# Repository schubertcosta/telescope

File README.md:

# telescope
My personal telescope project

#1 Step 1
    - check/change variables inside the constants.py

#2 Make sure your bluetooth is connected with your machine

#3 Run commands
    - Simulation mode: py -3.8 start.py
    - Analysis mode: py start.py -a

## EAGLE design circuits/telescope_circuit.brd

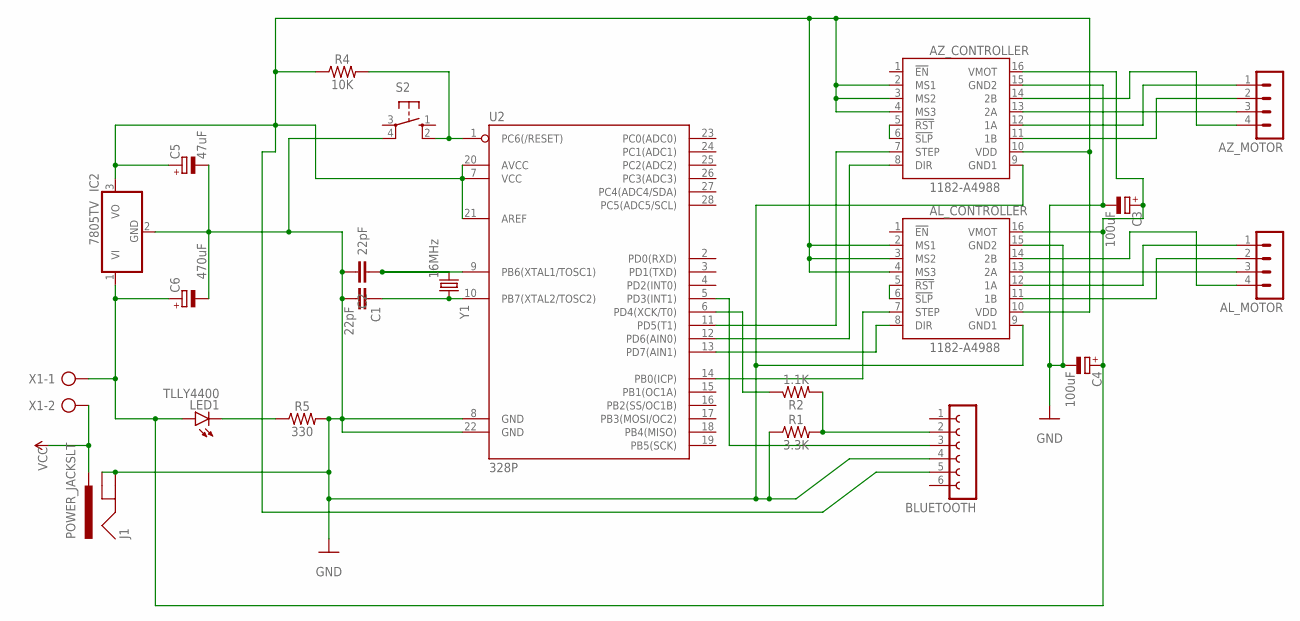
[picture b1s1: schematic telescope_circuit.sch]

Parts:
AL_CONTROLLER: 1182-A4988; A4988
AL_MOTOR: MA04-1
AZ_CONTROLLER: 1182-A4988; A4988
AZ_MOTOR: MA04-1
BLUETOOTH: FE06W
C1, C2: 22pF; CAP-PTH-2.54
C3, C4: 100uF; E2,5-6
C5: 47uF; E2,5-6
C6: 470uF; E2,5-6
IC2: 7805TV; TO220V
J1: POWER_JACKSLT; POWER_JACK_SLOT
LED1: TLLY4400; LED3MM
R1: 3.3K; AXIAL-0.3
R2: 1.1K; AXIAL-0.3
R4: 10K; AXIAL-0.3
R5: 330; AXIAL-0.3
S2: 10-XX; B3F-10XX
U2: 328P; DIP28
X1: AK500/2
Y1: 16MHz; HC49US

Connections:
GND: AL_CONTROLLER.9 (GND1), AL_CONTROLLER.15 (GND2), AZ_CONTROLLER.9 (GND1), AZ_CONTROLLER.15 (GND2), BLUETOOTH.4, C1.2, C2.2, C3.-, C4.-, C5.-, C6.-, IC2.2 (GND), J1.GND@1 (GNDBREAK), J1.GND@2 (GND), R1.P$1 (1), R5.P$2 (2), S2.4 (P1), U2.8 (GND), U2.22 (GND)
unnamed: C1.1, U2.10 (PB7(XTAL2/TOSC2)), Y1.2
unnamed: C2.1, U2.9 (PB6(XTAL1/TOSC1)), Y1.1
unnamed: AZ_CONTROLLER.7 (STEP), U2.11 (PD5(T1))
unnamed: BLUETOOTH.2, R1.P$2 (2), R2.P$2 (2)
unnamed: R4.P$2 (2), S2.2 (S1), U2.1 (PC6(/RESET))
unnamed: R2.P$1 (1), U2.6 (PD4(XCK/T0))
unnamed: AL_CONTROLLER.2 (MS1), AL_CONTROLLER.3 (MS2), AL_CONTROLLER.4 (MS3), AL_CONTROLLER.10 (VDD), AZ_CONTROLLER.2 (MS1), AZ_CONTROLLER.3 (MS2), AZ_CONTROLLER.4 (MS3), AZ_CONTROLLER.10 (VDD), BLUETOOTH.5, C5.+, IC2.3 (VO), R4.P$1 (1), U2.7 (VCC), U2.20 (AVCC), U2.21 (AREF)
unnamed: BLUETOOTH.3, U2.5 (PD3(INT1))
unnamed: AL_CONTROLLER.16 (VMOT), AZ_CONTROLLER.16 (VMOT), C3.+, C4.+, C6.+, IC2.1 (VI), LED1.A, X1.1
unnamed: AZ_CONTROLLER.8 (DIR), U2.12 (PD6(AIN0))
unnamed: AZ_CONTROLLER.5 (!RST), AZ_CONTROLLER.6 (!SLP)
unnamed: AZ_CONTROLLER.12 (1A), AZ_MOTOR.1
unnamed: AZ_CONTROLLER.11 (1B), AZ_MOTOR.2
unnamed: LED1.K (C), R5.P$1 (1)
unnamed: AZ_CONTROLLER.13 (2A), AZ_MOTOR.3
unnamed: AZ_CONTROLLER.14 (2B), AZ_MOTOR.4
unnamed: AL_CONTROLLER.8 (DIR), U2.13 (PD7(AIN1))
unnamed: AL_CONTROLLER.5 (!RST), AL_CONTROLLER.6 (!SLP)
unnamed: AL_CONTROLLER.7 (STEP), U2.14 (PB0(ICP))
unnamed: AL_CONTROLLER.12 (1A), AL_MOTOR.1
unnamed: AL_CONTROLLER.11 (1B), AL_MOTOR.2
unnamed: AL_CONTROLLER.13 (2A), AL_MOTOR.3
unnamed: AL_CONTROLLER.14 (2B), AL_MOTOR.4
VCC: J1.PWR, X1.2

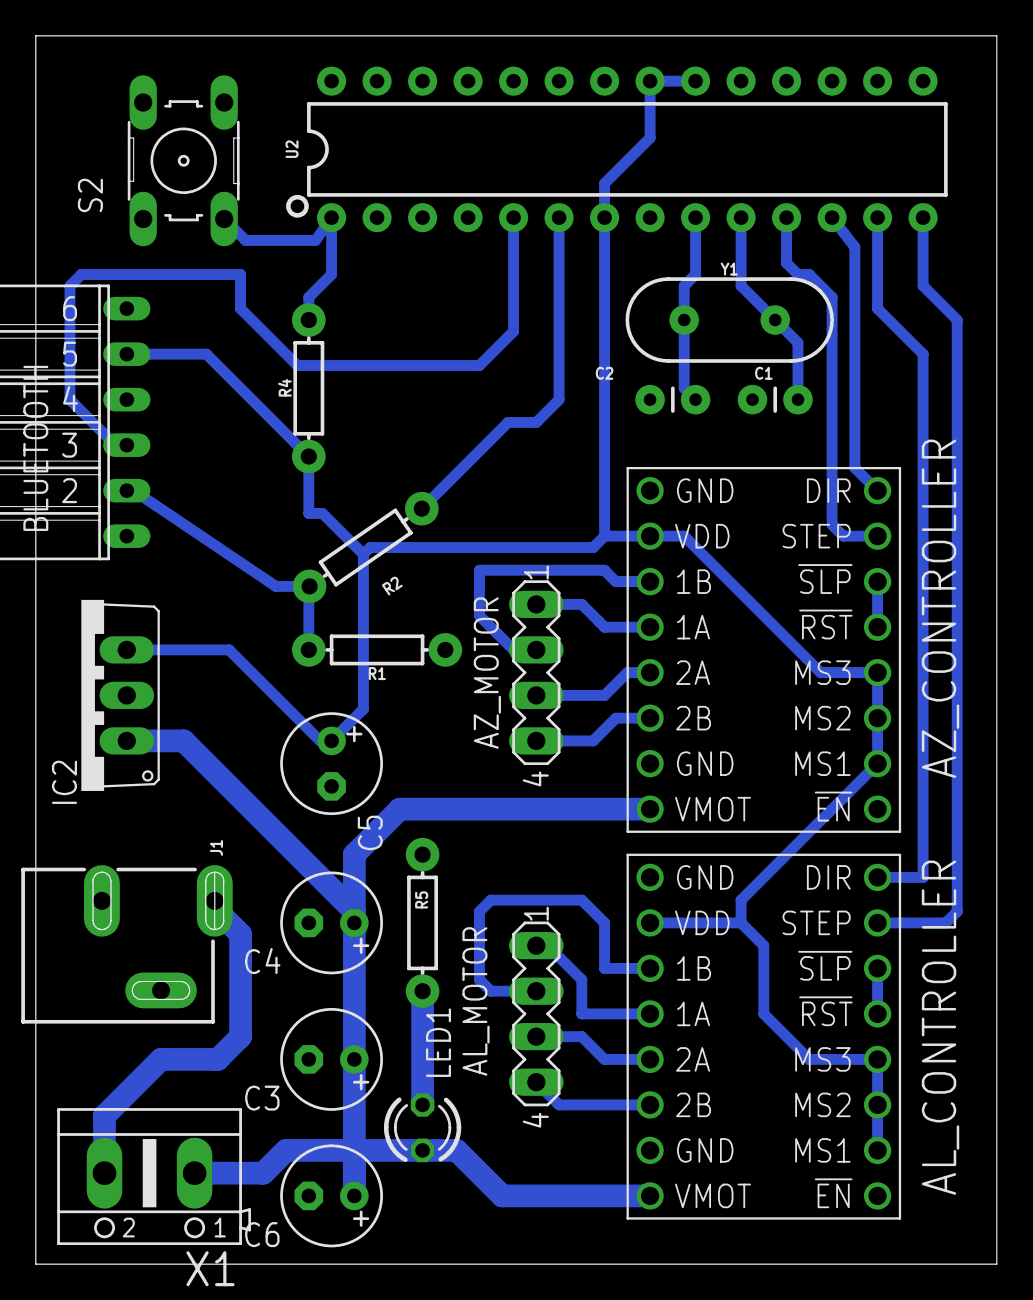
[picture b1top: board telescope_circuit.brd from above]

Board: 2 copper layers, 53.6 x 68.6 mm, 22 parts (0 on the bottom side), 25 nets.

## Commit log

2021-10-18 commiting first files
2021-10-18 first changes to start the loop
2021-10-19 small progress
2021-10-21 fixin problems
2021-10-21 finishing cinematics first steps
2021-10-24 performing improvements and applying new code
2021-10-24 last small change
2021-10-26 small chart changes
2021-11-11 integration with calculation of the parameters
2021-11-11 smaill fix
2021-11-13 improving code and fixing problem with last position
2021-11-13 live chart but still with bug
2021-11-14 finally finishing charts
2021-11-14 last adjust to the chart
2021-11-14 improving code and preparing calculating of best route with validations of range
2021-11-19 changes to fix calculation
2021-11-21 quick and dirty approach to fix ranges
2021-11-21 adding a new chart
2021-12-03 adding movement to the piece
2021-12-05 adding code for the freecad integration
2021-12-14 make telescope work with freecad
2021-12-14 setting chart to work again
2021-12-16 adding integration with freecad
2021-12-16 adding charts as well
2021-12-19 fixing problem of two threads
2021-12-19 fixing initial position
2021-12-19 refactoring code
2021-12-19 improving approach for each angles
2021-12-19 small fixes
2021-12-20 setting position chart to work together
2021-12-20 adding support to the charts
2021-12-20 starting calculations for velocity, aceleration and torque
2021-12-29 changes to retrieve data from velocitiy
2021-12-29 adding part of the code for caculate the torque
2021-12-29 missing only fix the last part of the energy diff
2021-12-30 trying to fix torque calculation
2021-12-30 saving before big change
2021-12-31 version which works the T1 for the base
2022-01-02 implementing changes
2022-01-02 finally fully working model
2022-01-02 changest o make it work with the new telescope version
2022-01-04 implementation using bluetooth
2022-01-05 performing data retrieval with arduino code and funciton in python
2022-01-08 improving implementation
2022-01-09 fixing ranges
2022-01-10 discoverying bugs and adding code for the firmware
2022-01-11 fixing modeling
2022-01-11 fixing issues and integrating bluetooth
2022-01-12 fixing problem with coordinates for az
2022-01-12 last changes implemented and fix in the formula to calculate motor rotation
2022-01-17 small fixes to the eagle pcb

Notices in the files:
parts and their libraries:
SparkFun-Capacitors: Licensing: Creative Commons ShareAlike 4.0 International - https://creativecommons.org/licenses/by-sa/4.0
